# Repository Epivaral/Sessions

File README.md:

# Sessions

This repository contains materials and demos for various technical sessions covering databases, IoT, AI, and PCB design topics.

## Session Contents

### [Azure Data Studio](./Azure%20Data%20Studio/)
Introduction to Azure Data Studio with hands-on demos including:
- Interactive Jupyter notebooks for data analysis
- SQL script examples and demonstrations
- Getting started presentation materials

### [Fundamentals of T-SQL Language](./Fundamentals%20of%20T-SQL%20language/)
Core concepts and fundamentals of T-SQL programming:
- T-SQL language basics and syntax
- Demo scripts for practical examples
- Comprehensive presentation on T-SQL fundamentals

### [GenAI Crea Apps Sin Saberlo Todo](./GenAI%20Crea%20apps%20sin%20saberlo%20todo/)
Generative AI session on creating applications without knowing everything:
- Visual diagrams and architecture designs
- AI-powered development concepts

### [Introducción a Diseño PCB](./Introduccion%20a%20diseno%20PCB/)
Introduction to PCB (Printed Circuit Board) design:
- PCB design fundamentals presentation
- Practical demo projects with schematics and board layouts
- KiCad project files for hands-on learning
- Fritzing breadboard and schematic examples

### [IoT Hub](./IoThub/)
Azure IoT Hub integration and development:
- IoT Hub introduction and concepts
- Arduino-based demo projects for device connectivity
- Windows Forms application for IoT device management
- Complete code examples for IoT device communication

### [MicroPython para IoT](./MicroPython%20para%20IoT/)
MicroPython programming for IoT devices:
- MicroPython fundamentals for IoT applications
- ESP8266 firmware and flashing instructions
- Hands-on demos covering sensors, displays, and web connectivity
- Real-world IoT project examples

### [Modern Datawarehouse in Azure](./Modern%20Datawarehouse%20in%20Azure/)
Modern data warehousing solutions using Azure services:
- Azure data warehouse architecture and best practices
- Modern approaches to data warehousing in the cloud

### [T-SQL Basics Coding for Performance](./T-SQL%20Basics%20coding%20for%20performance/)
Performance optimization techniques for T-SQL:
- T-SQL performance best practices
- Optimization strategies and coding techniques
- Performance-focused demo scripts and examples

---

Each session folder contains presentations, demo code, and supporting materials for hands-on learning and practical implementation.

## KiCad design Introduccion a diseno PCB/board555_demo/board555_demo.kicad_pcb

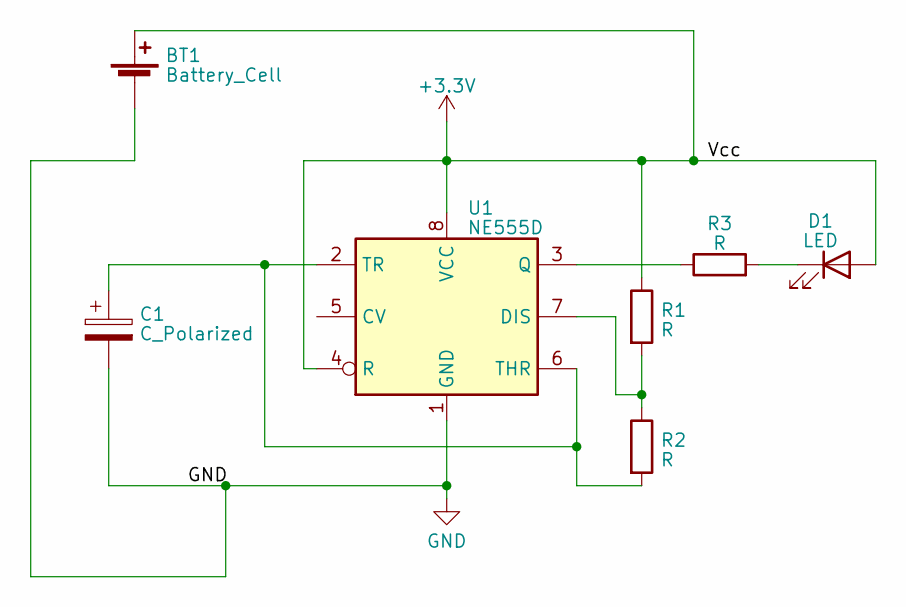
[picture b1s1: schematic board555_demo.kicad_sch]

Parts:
BT1: Battery_Cell; Battery_Panasonic_CR2025-V1AK_Vertical_CircularHoles
C1: C_Polarized; CP_Radial_D4.0mm_P2.00mm
D1: LED; LED_D5.0mm_Horizontal_O1.27mm_Z3.0mm
R1, R2, R3: R; R_0603_1608Metric
U1: NE555D; SOIC-8_3.9x4.9mm_P1.27mm

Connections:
+3.3V: BT1.1 (+), D1.2 (A), R1.1, U1.4 (R), U1.8 (VCC)
GND: BT1.2 (-), C1.2, U1.1 (GND)
unnamed: D1.1 (K), R3.2
unnamed: R1.2, R2.1, U1.7 (DIS)
unnamed: R3.1, U1.3 (Q)
unnamed: C1.1, R2.2, U1.2 (TR), U1.6 (THR)

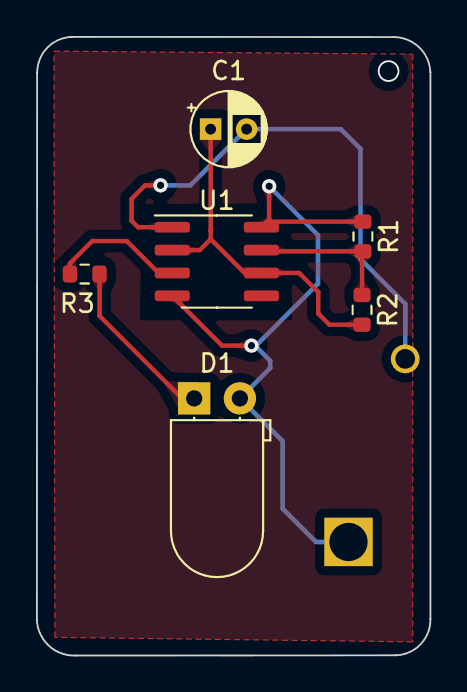
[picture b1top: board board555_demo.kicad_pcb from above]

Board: 2 copper layers, 21.9 x 34.4 mm, 7 parts (1 on the bottom side), 6 nets.

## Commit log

2020-05-01 upload demos
2020-05-01 updated sessions
2020-09-26 Updated files
2020-11-26 Delete T-SQL Basics coding for performance V2.pptx
    outdated version
2020-11-26 Add files via upload
    updated version, fixed some typos
2020-11-26 Add files via upload
    latest version
2021-02-01 CodeCamp 2021
2022-06-22 Bump Newtonsoft.Json in /IoThub/WinformsIoT/WinformsIoT
    Bumps [Newtonsoft.Json](https://github.com/JamesNK/Newtonsoft.Json) from 12.0.3 to 13.0.1.
    - [Release notes](https://github.com/JamesNK/Newtonsoft.Json/releases)
    - [Commits](https://github.com/JamesNK/Newtonsoft.Json/compare/12.0.3...13.0.1)
    ---
    updated-dependencies:
    - dependency-name: Newtonsoft.Json
2022-08-27 Bump Microsoft.Owin in /IoThub/WinformsIoT/WinformsIoT
    Bumps [Microsoft.Owin](https://github.com/aspnet/AspNetKatana) from 4.0.0 to 4.1.1.
    - [Release notes](https://github.com/aspnet/AspNetKatana/releases)
    - [Commits](https://github.com/aspnet/AspNetKatana/compare/v4.0.0...v4.1.1)
    ---
    updated-dependencies:
    - dependency-name: Microsoft.Owin
2022-08-31 Bump Microsoft.Owin in /IoThub/WinformsIoT/WinformsIoT
    Bumps [Microsoft.Owin](https://github.com/aspnet/AspNetKatana) from 4.0.0 to 4.2.2.
    - [Release notes](https://github.com/aspnet/AspNetKatana/releases)
    - [Commits](https://github.com/aspnet/AspNetKatana/compare/v4.0.0...v4.2.2)
    ---
    updated-dependencies:
    - dependency-name: Microsoft.Owin
2022-12-08 Bump Newtonsoft.Json in /IoThub/WinformsIoT/WinformsIoT
    Bumps [Newtonsoft.Json](https://github.com/JamesNK/Newtonsoft.Json) from 12.0.3 to 13.0.2.
    - [Release notes](https://github.com/JamesNK/Newtonsoft.Json/releases)
    - [Commits](https://github.com/JamesNK/Newtonsoft.Json/compare/12.0.3...13.0.2)
    ---
    updated-dependencies:
    - dependency-name: Newtonsoft.Json
2023-03-23 PCB de demo
    PCB de demo, no esta optimizada, unicamente muestra las funcionalidades de la herramienta
2025-07-08 Update README.md to include detailed session contents and descriptions
